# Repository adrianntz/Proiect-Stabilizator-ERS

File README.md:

# Proiect-Stabilizator-ERS
Proiect universitar creeat cu scopul de a studia proiectarea unui stabilizator de tensiune cu element de reglaj serie.

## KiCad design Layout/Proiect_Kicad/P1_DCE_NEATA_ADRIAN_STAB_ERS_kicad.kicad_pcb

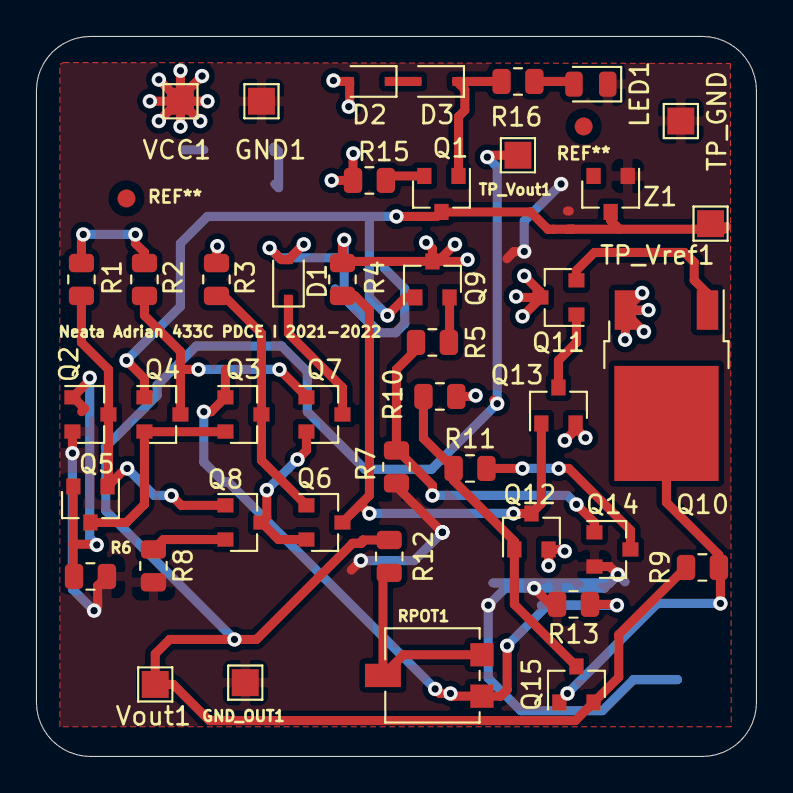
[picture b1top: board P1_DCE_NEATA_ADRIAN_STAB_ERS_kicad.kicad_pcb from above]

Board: 2 copper layers, 40.0 x 40.0 mm, 43 parts (0 on the bottom side), 26 nets.

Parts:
D1, D2, D3: 1N4148WS; D_SOD-323F
GND1: TestPoint; TestPoint_Pad_1.5x1.5mm
GND_OUT1: TestPoint; TestPoint_Pad_1.5x1.5mm
LED1: LED; LED_0805_2012Metric
Q1, Q12, Q13: BC857; SOT-23
Q2, Q3, Q4, Q5, Q6, Q7, Q8, Q9, Q11, Q14, Q15: BC847; SOT-23
Q10: MJD44E3T4G; TO-252-2
R1: 3k3; R_0805_2012Metric
R2, R3, R16: 2k; R_0805_2012Metric
R4: 300; R_0805_2012Metric
R5: 16k; R_0805_2012Metric
R6, R8: 175; R_0805_2012Metric
R7: 3k57; R_0805_2012Metric
R9: 1.5; R_0805_2012Metric
R10, R11: 4k7; R_0805_2012Metric
R12: 32.4k; R_0805_2012Metric
R13: 18k; R_0805_2012Metric
R15: 150; R_0805_2012Metric
RPOT1: 50k; Potentiometer_Vishay_TS53YL_Vertical
TP_GND: TestPoint; TestPoint_Pad_1.5x1.5mm
TP_Vout1: TestPoint; TestPoint_Pad_1.5x1.5mm
TP_Vref1: TestPoint; TestPoint_Pad_1.5x1.5mm
VCC1: TestPoint; TestPoint_Pad_1.5x1.5mm
Vout1: TestPoint; TestPoint_Pad_1.5x1.5mm
Z1: BZX84-B3V0; D_SOT-23_ANK

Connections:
GND: GND1.1, GND_OUT1.1, LED1.1, Q2.2, Q14.2, R6.2, R7.2, R8.2, R13.2, TP_GND.1, Z1.2
unnamed: D1.1, Q7.3
unnamed: D2.1, D3.2
unnamed: D3.1, Q1.1, R16.1
unnamed: LED1.2, R16.2
unnamed: Q1.2, R15.2
unnamed: Q2.1, Q5.2, R6.1
unnamed: Q2.3, Q5.1, Q8.1, R1.2
unnamed: Q3.2, Q4.2, Q5.3
unnamed: Q3.3, Q6.1, R3.2
unnamed: Q4.3, Q7.1, R2.2
unnamed: Q6.2, Q7.2, Q8.3
unnamed: Q8.2, R8.1
unnamed: Q9.2, R5.1
unnamed: Q10.1, Q11.2
unnamed: Q11.1, Q13.3
unnamed: Q12.1, Q15.3, R10.2, R11.1
unnamed: Q14.1, R5.2, R7.1
unnamed: Q14.3, R11.2
unnamed: R12.2, RPOT1.1, RPOT1.2
VDC: D1.2, D2.2, Q9.3, Q10.3, Q11.3, Q12.2, Q13.2, R1.1, R2.1, R3.1, R4.1, R10.1, R15.1, VCC1.1
Vdif: Q6.3, Q12.3, Q13.1, R4.2
Vout: Q15.2, R9.1, R12.1, TP_Vout1.1, Vout1.1
Vref: Q1.3, Q4.1, Q9.1, TP_Vref1.1, Z1.1
Vref2: Q3.1, R13.1, RPOT1.3
Vrsc1: Q10.2, Q15.1, R9.2

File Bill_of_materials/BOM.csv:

"Id";"Designator";"Package";"Quantity";"Designation";"Supplier and ref";
1;"TP_GND,GND1,GND_OUT1,VCC1,Vout1,TP_Vout1,TP_Vref1";"TestPoint_Pad_1.5x1.5mm";7;"TestPoint";;;
2;"REF**,REF**";"Fiducial_1mm_Mask2mm";2;"Fiducial_1mm_Mask2mm";;;
3;"D1,D2,D3";"D_SOD-323F";3;"1N4148WS";;;
4;"LED1";"LED_0805_2012Metric";1;"LED";;;
5;"Q1,Q12,Q13";"SOT-23";3;"BC857";;;
6;"Q2,Q3,Q4,Q5,Q6,Q7,Q8,Q9,Q11,Q14,Q15";"SOT-23";11;"BC847";;;
7;"Q10";"TO-252-2";1;"MJD44E3T4G";;;
8;"R1";"R_0805_2012Metric";1;"3k3";;;
9;"R2,R3,R16";"R_0805_2012Metric";3;"2k";;;
10;"R4";"R_0805_2012Metric";1;"300";;;
11;"R5";"R_0805_2012Metric";1;"16k";;;
12;"R6,R8";"R_0805_2012Metric";2;"175";;;
13;"R7";"R_0805_2012Metric";1;"3k57";;;
14;"R9";"R_0805_2012Metric";1;"1.5";;;
15;"R10,R11";"R_0805_2012Metric";2;"4k7";;;
16;"R12";"R_0805_2012Metric";1;"32.4k";;;
17;"R13";"R_0805_2012Metric";1;"18k";;;
18;"R15";"R_0805_2012Metric";1;"150";;;
19;"RPOT1";"Potentiometer_Vishay_TS53YL_Vertical";1;"50k";;;
20;"Z1";"D_SOT-23_ANK";1;"BZX84-B3V0";;;

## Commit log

2022-06-09 Added initial files, including the KiCAD project files, TINA-TI simulations files and documentations
